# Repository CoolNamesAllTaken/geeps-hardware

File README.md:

# geeps-hardware
Pronounced Gee-Pee-Ess (hardware).

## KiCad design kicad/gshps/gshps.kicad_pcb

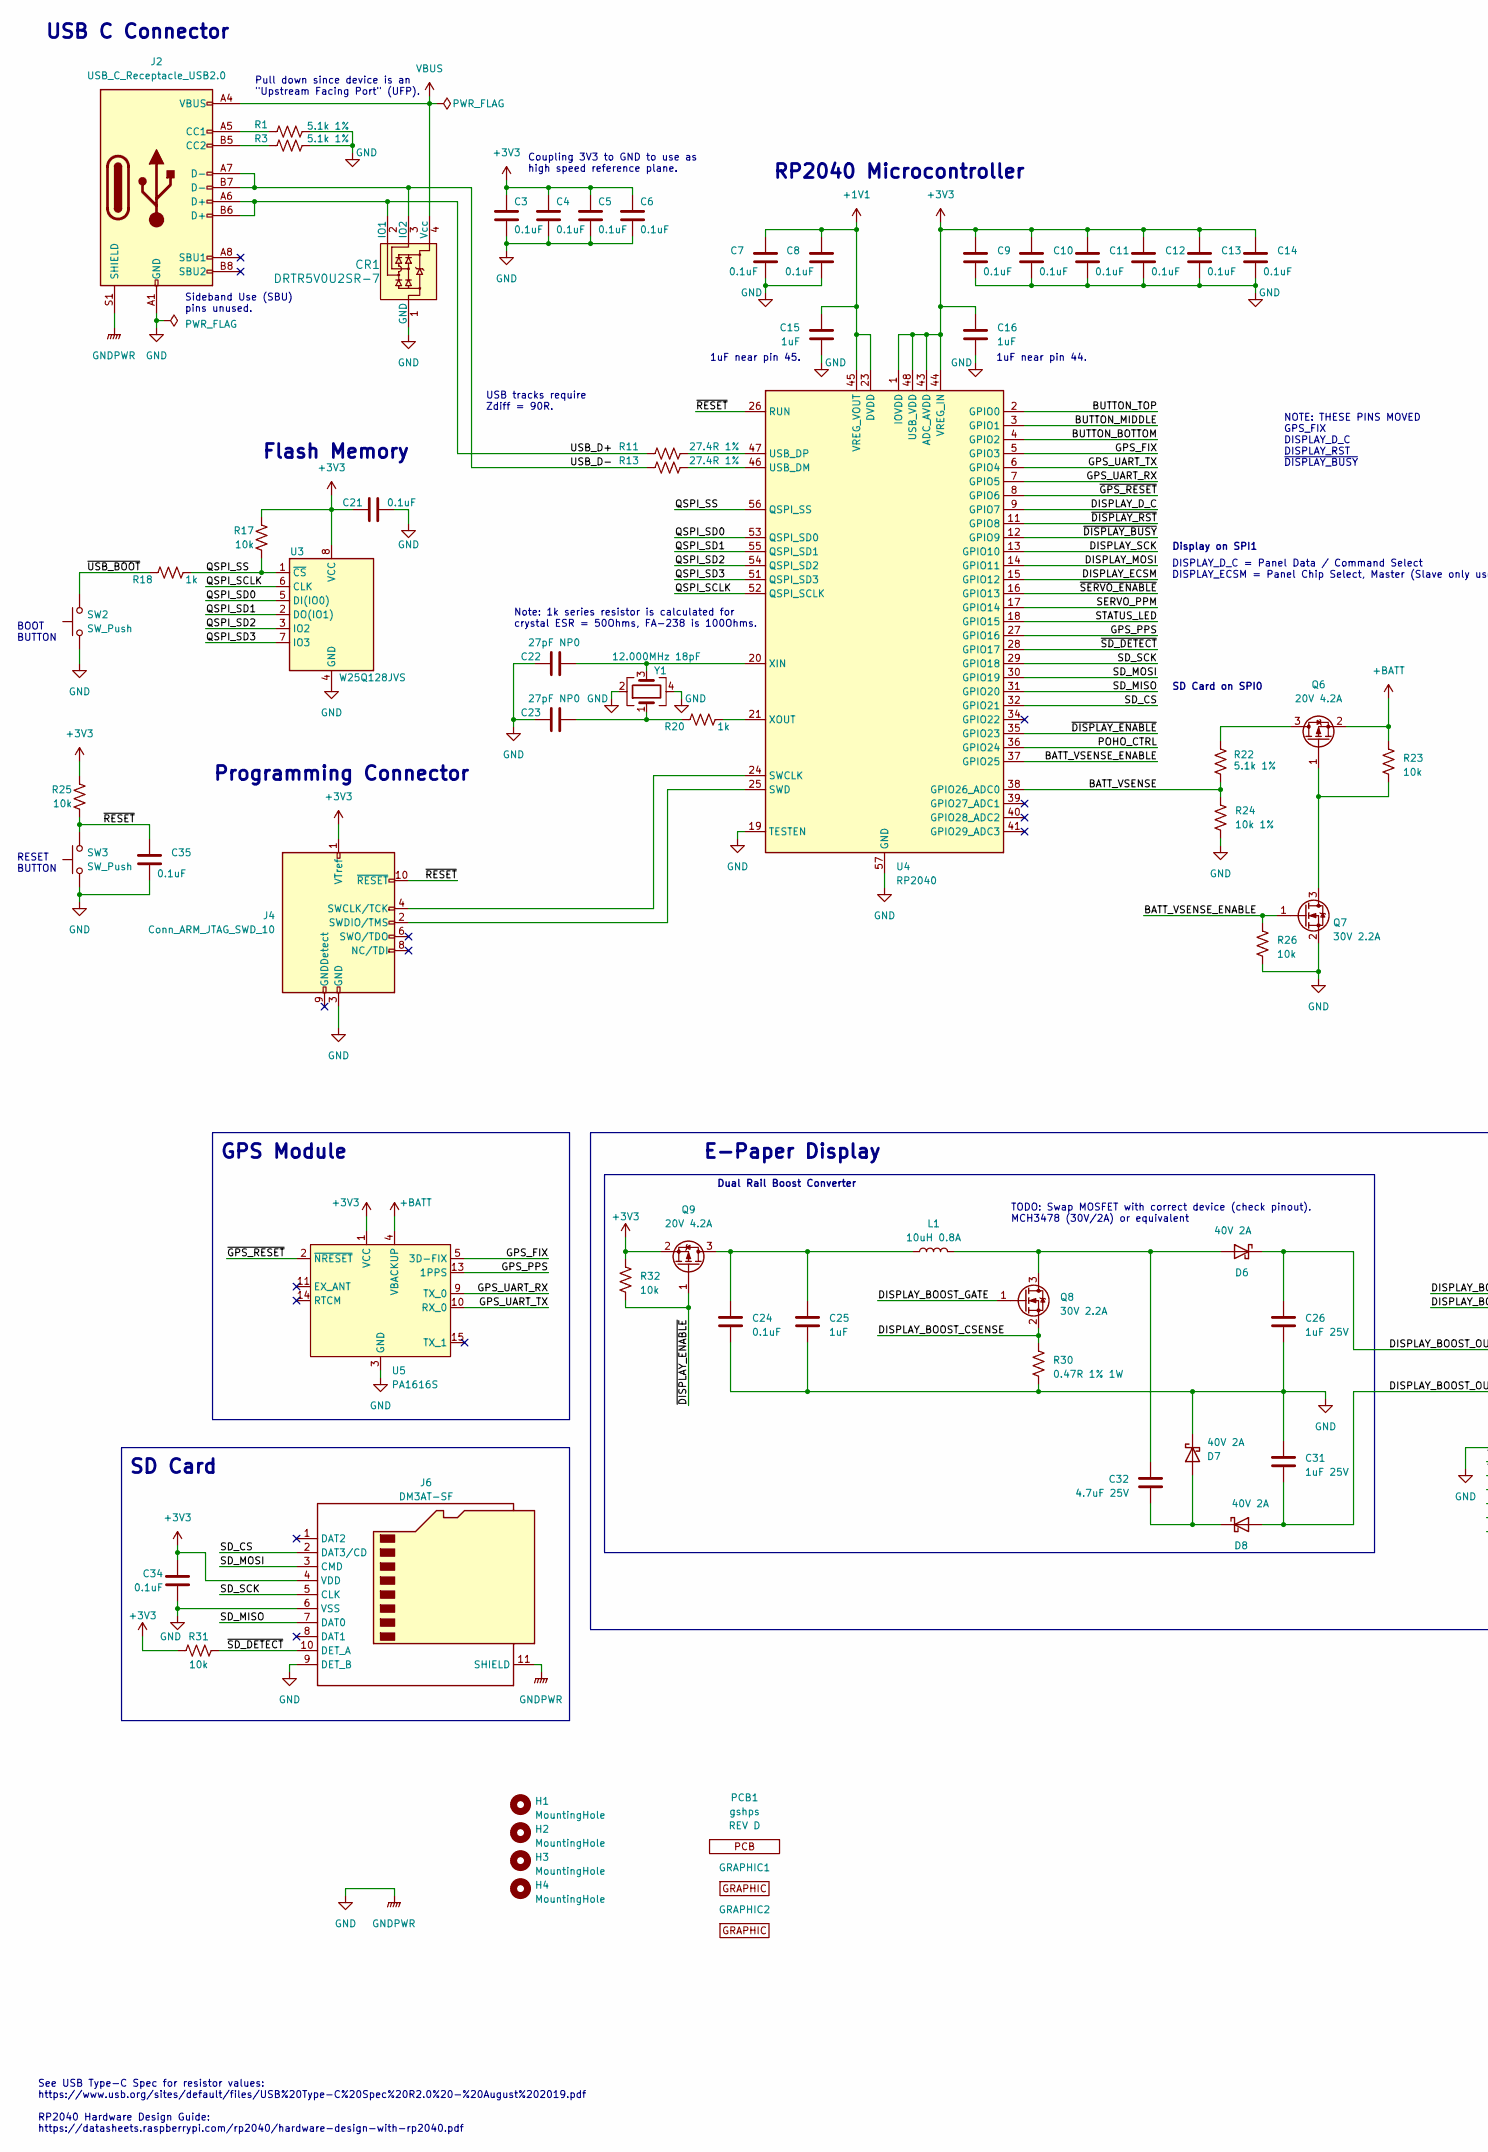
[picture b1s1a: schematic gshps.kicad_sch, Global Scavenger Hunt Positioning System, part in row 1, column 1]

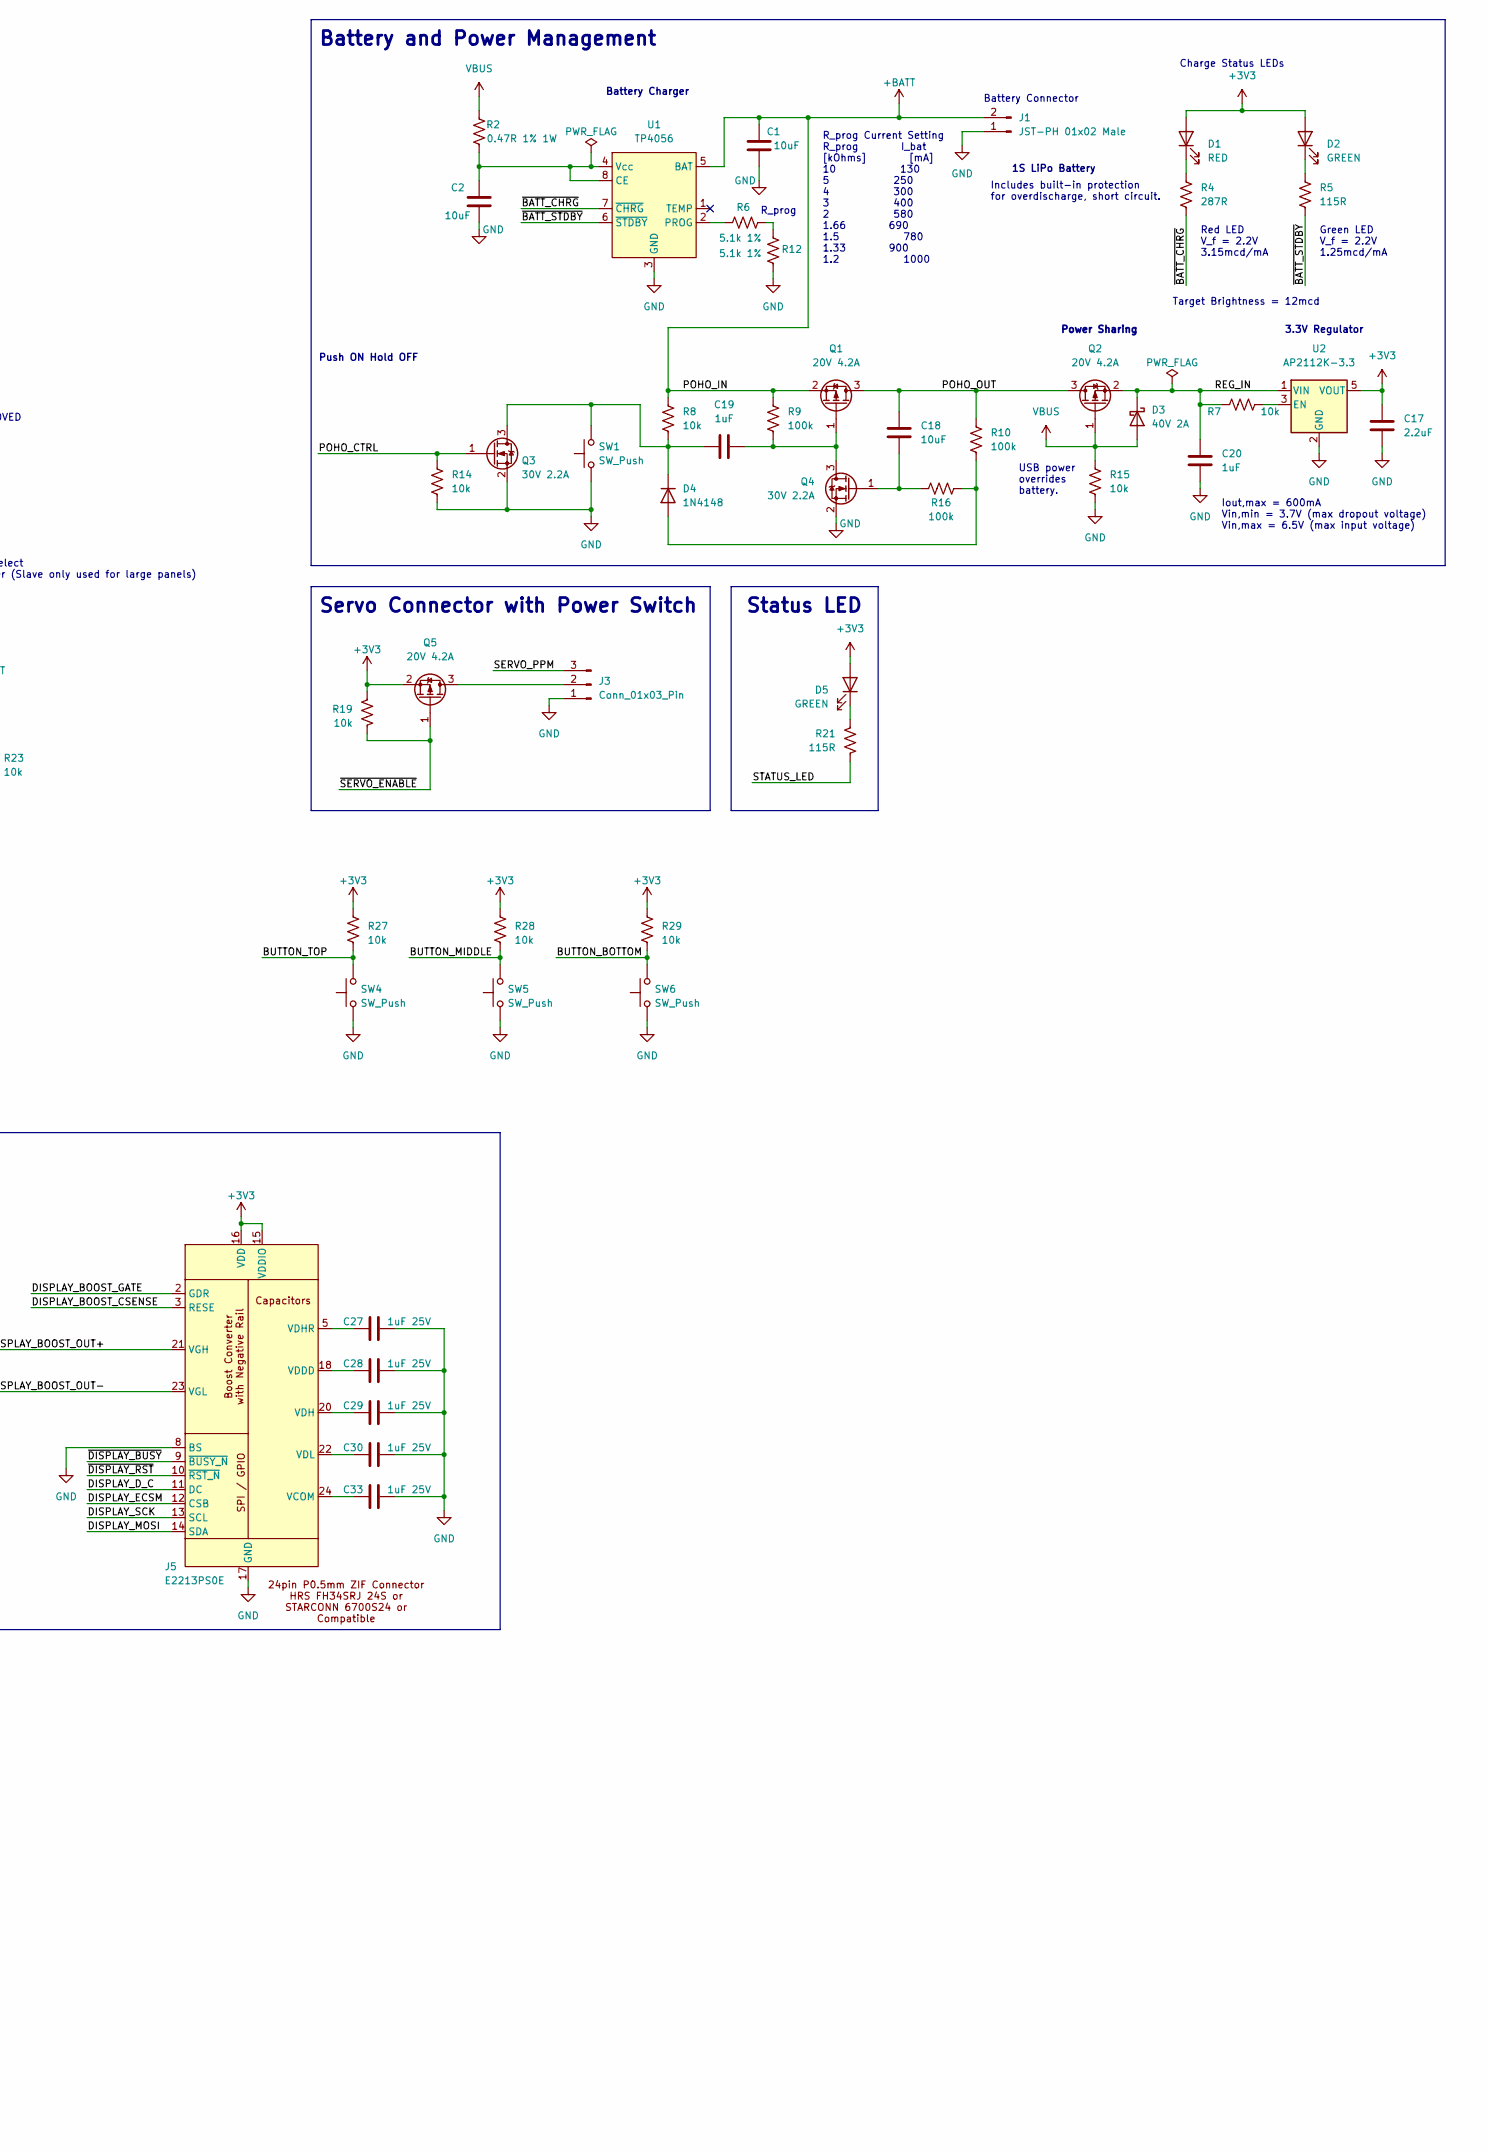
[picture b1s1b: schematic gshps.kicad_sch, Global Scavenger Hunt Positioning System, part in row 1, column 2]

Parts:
C1, C2, C18: 10uF; C_0805_2012Metric
C3, C4, C5, C6, C7, C8, C9, C10, C11, C12, C13, C14, C21, C24, C34, C35: 0.1uF; C_0402_1005Metric
C15, C16, C19, C20, C25: 1uF; C_0603_1608Metric
C17: 2.2uF; C_0603_1608Metric
C22, C23: 27pF NP0; C_0402_1005Metric
C26, C27, C28, C29, C30, C31, C33: 1uF 25V; C_0603_1608Metric
C32: 4.7uF 25V; C_0805_2012Metric
CR1: DRTR5V0U2SR-7; SOT-143; MPN DRTR5V0U2SR-7
D1: RED; LED_0603_1608Metric; MPN SML-D12U8WT86
D2, D5: GREEN; LED_0603_1608Metric; MPN SML-D12M8WT86
D3, D6, D7, D8: 40V 2A; D_SOD-123F; MPN SS2040FL_R1_00001
D4: 1N4148; D_SOD-123
GRAPHIC1: Graphic; BirdWithPants_Small_Right
GRAPHIC2: Graphic; BirdWithPants_Small_Left
H1, H2, H3, H4: MountingHole; MountingHole_2.7mm_M2.5_Isolated
J1: JST-PH 01x02 Male; JST_PH_S2B-PH-K_1x02_P2.00mm_Horizontal; MPN S2B-PH-K-S(LF)(SN)
J2: USB_C_Receptacle_USB2.0; USB_C_Receptacle_GCT_USB4115-03-C; MPN USB4115-03-C
J3: Conn_01x03_Pin; Molex_PicoBlade_53261-0371_1x03-1MP_P1.25mm_Horizontal; MPN 0532610371
J4: Conn_ARM_JTAG_SWD_10; PinHeader_2x05_P1.27mm_Vertical_SMD; MPN 4048
J5: E2213PS0E; Hirose_FH34SRJ-24S-0.5SH_1x24-1MP_P0.50mm_Horizontal_Mirror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; MPN FH34SRJ-24S-0.5SH(50)
J6: DM3AT-SF; microSD_HC_Hirose_DM3D-SF; MPN DM3AT-SF-PEJM5
L1: 10uH 0.8A; L_1008_2520Metric; MPN 74479887310A
PCB1: PCB; PCB_PN_REV; MPN gshps
Q1, Q2, Q5, Q6, Q9: 20V 4.2A; SOT-23; MPN DMG2305UX-7
Q3, Q4, Q7, Q8: 30V 2.2A; SOT-23; MPN DMN3200U-7
R1, R3, R6, R12, R22: 5.1k 1%; R_0402_1005Metric
R2, R30: 0.47R 1% 1W; R_2512_6332Metric; MPN RL2512FK-070R47L
R4: 287R; R_0402_1005Metric; MPN RC0402FR-07287RL
R5, R21: 115R; R_0402_1005Metric; MPN RC0402FR-07115RL
R7, R8, R14, R15, R17, R19, R23, R25, R26, R27, R28, R29, R31, R32: 10k; R_0402_1005Metric
R9, R10, R16: 100k; R_0402_1005Metric
R11, R13: 27.4R 1%; R_0402_1005Metric
R18, R20: 1k; R_0402_1005Metric
R24: 10k 1%; R_0402_1005Metric
SW1, SW2, SW3, SW4, SW5, SW6: SW_Push; SW_SPST_TL3342; MPN TL3342F160QG/TR
U1: TP4056; HSOP-8-1EP_3.9x4.9mm_P1.27mm_EP2.41x3.1mm_ThermalVias
U2: AP2112K-3.3; SOT-23-5; MPN AP2112K-3.3TRG1
U3: W25Q128JVS; SOIC-8_5.23x5.23mm_P1.27mm
U4: RP2040; QFN-56-1EP_7x7mm_P0.4mm_EP3.2x3.2mm
U5: PA1616S; MPN PA1616S
Y1: 12.000MHz 18pF; Crystal_SMD_SeikoEpson_FA238-4Pin_3.2x2.5mm; MPN FA-238V 12.0000MA-C5

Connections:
+1V1: C7.2, C8.2, C15.2, U4.23 (DVDD), U4.45 (VREG_VOUT), U4.50 (DVDD)
+3V3: C3.2, C4.2, C5.2, C6.2, C9.2, C10.2, C11.2, C12.2, C13.2, C14.2, C16.2, C17.1, C21.1, C34.1, D1.2 (A), D2.2 (A), D5.2 (A), J4.1 (VTref), J5.15 (VDDIO), J5.16 (VDD), J6.4 (VDD), Q5.2 (S), Q9.2 (S), R17.1, R19.1, R25.1, R27.1, R28.1, R29.1, R31.1, R32.1, U2.5 (VOUT), U3.8 (VCC), U4.1 (IOVDD), U4.10 (IOVDD), U4.22 (IOVDD), U4.33 (IOVDD), U4.42 (IOVDD), U4.43 (ADC_AVDD), U4.44 (VREG_IN), U4.48 (USB_VDD), U4.49 (IOVDD), U5.1 (VCC)
+BATT: C1.1, J1.2, Q1.2 (S), Q6.2 (S), R8.1, R9.1, R23.1, U1.5 (BAT), U5.4 (VBACKUP)
/BATT_VSENSE: R22.1, R24.1, U4.38 (GPIO26_ADC0)
/BATT_VSENSE_ENABLE: Q7.1 (G), R26.1, U4.37 (GPIO25)
/BUTTON_BOTTOM: R29.2, SW6.2, U4.4 (GPIO2)
/BUTTON_MIDDLE: R28.2, SW5.2, U4.3 (GPIO1)
/BUTTON_TOP: R27.2, SW4.2, U4.2 (GPIO0)
/DISPLAY_BOOST_CSENSE: J5.3 (RESE), Q8.2 (S), R30.1
/DISPLAY_BOOST_GATE: J5.2 (GDR), Q8.1 (G)
/DISPLAY_BOOST_OUT+: C26.1, D6.1 (K), J5.21 (VGH)
/DISPLAY_BOOST_OUT-: C31.2, D8.2 (A), J5.23 (VGL)
/DISPLAY_D_C: J5.11 (DC), U4.9 (GPIO7)
/DISPLAY_ECSM: J5.12 (CSB), U4.15 (GPIO12)
/DISPLAY_MOSI: J5.14 (SDA), U4.14 (GPIO11)
/DISPLAY_SCK: J5.13 (SCL), U4.13 (GPIO10)
/GPS_FIX: U4.5 (GPIO3), U5.5 (3D-FIX)
/GPS_PPS: U4.27 (GPIO16), U5.13 (1PPS)
/GPS_UART_RX: U4.7 (GPIO5), U5.9 (TX_0)
/GPS_UART_TX: U4.6 (GPIO4), U5.10 (RX_0)
/POHO_CTRL: Q3.1 (G), R14.1, U4.36 (GPIO24)
/POHO_OUT: C18.1, Q1.3 (D), Q2.3 (D), R10.1
/QSPI_SCLK: U3.6 (CLK), U4.52 (QSPI_SCLK)
/QSPI_SD0: U3.5 (DI(IO0)), U4.53 (QSPI_SD0)
/QSPI_SD1: U3.2 (DO(IO1)), U4.55 (QSPI_SD1)
/QSPI_SD2: U3.3 (IO2), U4.54 (QSPI_SD2)
/QSPI_SD3: U3.7 (IO3), U4.51 (QSPI_SD3)
/QSPI_SS: R17.2, R18.2, U3.1 (~CS), U4.56 (QSPI_SS)
/REG_IN: C20.1, D3.1 (K), Q2.2 (S), R7.1, U2.1 (VIN)
/SD_CS: J6.2 (DAT3/CD), U4.32 (GPIO21)
/SD_MISO: J6.7 (DAT0), U4.31 (GPIO20)
/SD_MOSI: J6.3 (CMD), U4.30 (GPIO19)
/SD_SCK: J6.5 (CLK), U4.29 (GPIO18)
/SERVO_PPM: J3.3, U4.17 (GPIO14)
/STATUS_LED: R21.2, U4.18 (GPIO15)
/USB_D+: CR1.2 (IO1), J2.A6 (D+), J2.B6 (D+), R11.1
/USB_D-: CR1.3 (IO2), J2.A7 (D-), J2.B7 (D-), R13.1
/~BATT_CHRG: R4.2, U1.7 (~CHRG)
/~BATT_STDBY: R5.2, U1.6 (~STDBY)
/~DISPLAY_BUSY: J5.9 (~BUSY_N), U4.12 (GPIO9)
/~DISPLAY_ENABLE: Q9.1 (G), R32.2, U4.35 (GPIO23)
/~DISPLAY_RST: J5.10 (~RST_N), U4.11 (GPIO8)
/~GPS_RESET: U4.8 (GPIO6), U5.2 (~NRESET)
/~RESET: C35.2, J4.10 (~RESET), R25.2, SW3.2, U4.26 (RUN)
/~SD_DETECT: J6.10 (DET_A), R31.2, U4.28 (GPIO17)
/~SERVO_ENABLE: Q5.1 (G), R19.2, U4.16 (GPIO13)
/~USB_BOOT: R18.1, SW2.2
GND: C1.2, C2.2, C3.1, C4.1, C5.1, C6.1, C7.1, C8.1, C9.1, C10.1, C11.1, C12.1, C13.1, C14.1, C15.1, C16.1, C17.2, C20.2, C21.2, C22.1, C23.1, C24.2, C25.2, C26.2, C27.2, C28.2, C29.2, C30.2, C31.1, C33.2, C34.2, C35.1, CR1.1 (GND), D7.1 (K), J1.1, J2.A1 (GND), J2.A12 (GND), J2.B1 (GND), J2.B12 (GND), J2.S1 (SHIELD), J3.1, J4.3 (GND), J4.5 (GND), J5.8 (BS), J5.17 (GND), J6.6 (VSS), J6.9 (DET_B), J6.11 (SHIELD), Q3.2 (S), Q4.2 (S), Q7.2 (S), R1.2, R3.2, R12.1, R14.2, R15.2, R24.2, R26.2, R30.2, SW1.1, SW2.1, SW3.1, SW4.1, SW5.1, SW6.1, U1.3 (GND), U1.9 (GND), U2.2 (GND), U3.4 (GND), U4.19 (TESTEN), U4.57 (GND), U5.3 (GND), U5.8 (GND), U5.12 (GND), U5.19 (GND), Y1.2, Y1.4
unnamed: C23.2, R20.1, Y1.1
unnamed: D1.1 (K), R4.1
unnamed: D2.1 (K), R5.1
unnamed: D4.2 (A), R10.2, R16.2
unnamed: C19.1, D4.1 (K), Q3.3 (D), R8.2, SW1.2
unnamed: D5.1 (K), R21.1
unnamed: C32.1, D6.2 (A), L1.2, Q8.3 (D)
unnamed: C32.2, D7.2 (A), D8.1 (K)
unnamed: J2.A5 (CC1), R1.1
unnamed: J2.B5 (CC2), R3.1
unnamed: J3.2, Q5.3 (D)
unnamed: J4.4 (SWCLK/TCK), U4.24 (SWCLK)
unnamed: J4.2 (SWDIO/TMS), U4.25 (SWD)
unnamed: C33.1, J5.24 (VCOM)
unnamed: C28.1, J5.18 (VDDD)
unnamed: C29.1, J5.20 (VDH)
unnamed: C27.1, J5.5 (VDHR)
unnamed: C30.1, J5.22 (VDL)
unnamed: C19.2, Q1.1 (G), Q4.3 (D), R9.2
unnamed: C18.2, Q4.1 (G), R16.1
unnamed: Q6.3 (D), R22.2
unnamed: Q6.1 (G), Q7.3 (D), R23.2
unnamed: C24.1, C25.1, L1.1, Q9.3 (D)
unnamed: R6.2, R12.2
unnamed: C2.1, R2.2, U1.4 (Vcc), U1.8 (CE)
unnamed: R6.1, U1.2 (PROG)
unnamed: R7.2, U2.3 (EN)
unnamed: R13.2, U4.46 (USB_DM)
unnamed: R11.2, U4.47 (USB_DP)
unnamed: C22.2, U4.20 (XIN), Y1.3
unnamed: R20.2, U4.21 (XOUT)
VBUS: CR1.4 (Vcc), D3.2 (A), J2.A4 (VBUS), J2.A9 (VBUS), J2.B4 (VBUS), J2.B9 (VBUS), Q2.1 (G), R2.1, R15.1

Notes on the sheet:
NOTE: THESE PINS MOVED GPS_FIX DISPLAY_D_C DISPLAY_RST ~{DISPLAY_BUSY}
Flash Memory
1uF near pin 45.
Red LED V_f = 2.2V 3.15mcd/mA
Battery Connector
TODO: Swap MOSFET with correct device (check pinout). MCH3478 (30V/2A) or equivalent
DISPLAY_D_C = Panel Data / Command Select DISPLAY_ECSM = Panel Chip Select, Master (Slave only used for large panels)
SD Card
USB power overrides battery.
3.3V Regulator
USB tracks require Zdiff = 90R.
Battery Charger
Power Sharing
Iout,max = 600mA Vin,min = 3.7V (max dropout voltage) Vin,max = 6.5V (max input voltage)
Battery and Power Management
Push ON Hold OFF
Servo Connector with Power Switch
Green LED V_f = 2.2V 1.25mcd/mA
GPS Module
Display on SPI1
Status LED
Dual Rail Boost Converter
Coupling 3V3 to GND to use as high speed reference plane.
SD Card on SPI0
RESET BUTTON
Charge Status LEDs
Programming Connector
BOOT BUTTON
1uF near pin 44.
E-Paper Display
RP2040 Microcontroller
Note: 1k series resistor is calculated for crystal ESR = 50Ohms, FA-238 is 100Ohms.
Target Brightness = 12mcd
R_prog Current Setting R_prog I_bat [kOhms] [mA] 10 130 5 250 4 300 3 400 2 580 1.66 690 1.5 780 1.33 900 1.2 1000
R_prog
Sideband Use (SBU) pins unused.
Includes built-in protection for overdischarge, short circuit.
See USB Type-C Spec for resistor values: https://www.usb.org/sites/default/files/USB%20Type-C%20Spec%20R2.0%20-%20August%202019.pdf RP2040 Hardware Design Guide: https://datasheets.raspberrypi.com/rp2040/hardware-design-with-rp2040.pdf
1S LiPo Battery
USB C Connector

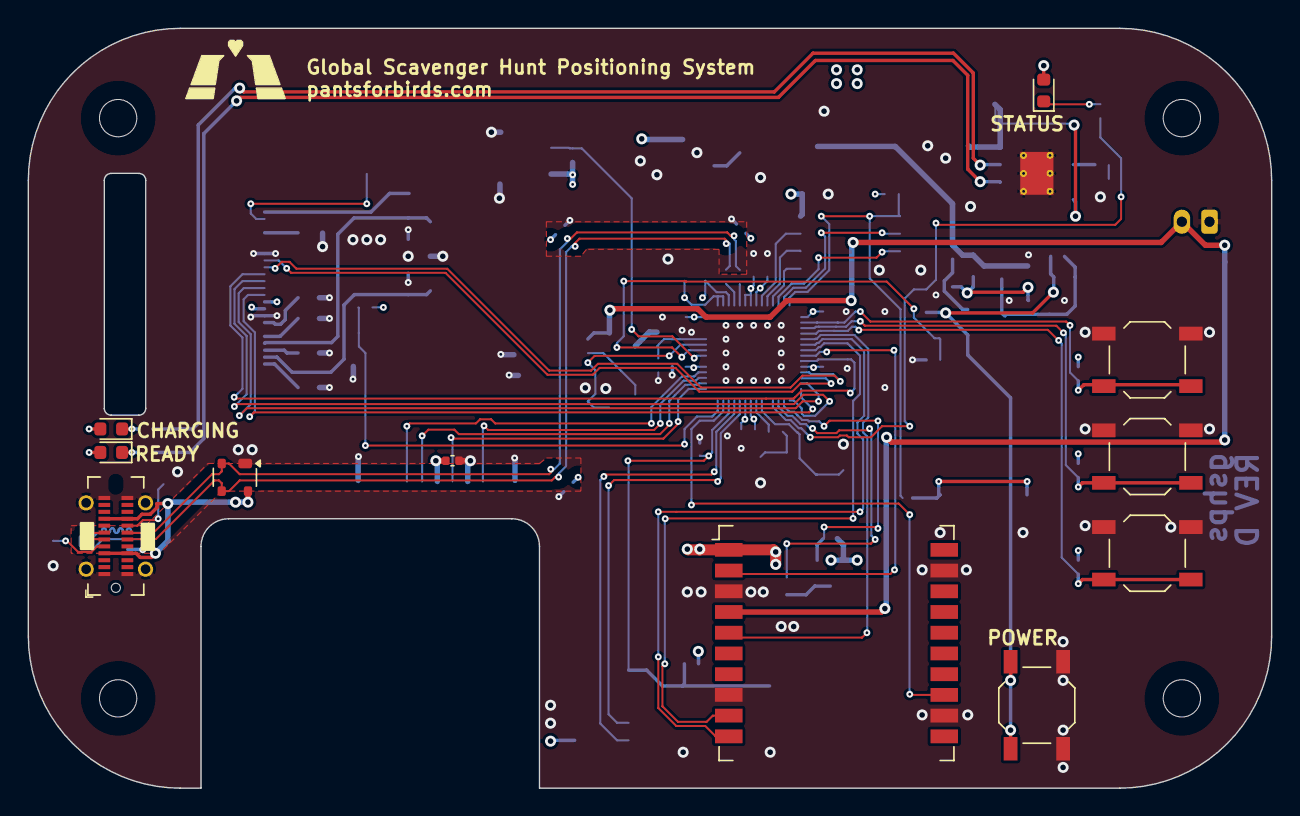
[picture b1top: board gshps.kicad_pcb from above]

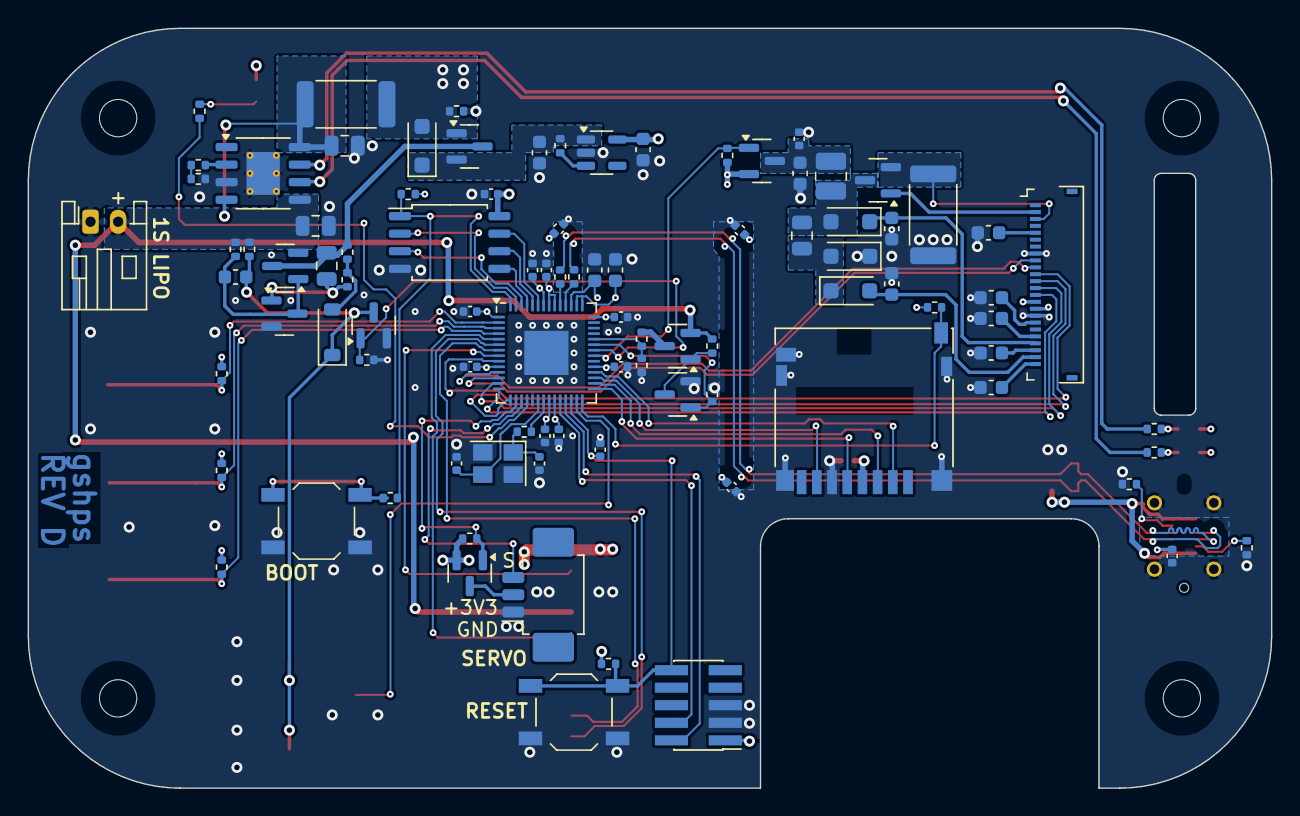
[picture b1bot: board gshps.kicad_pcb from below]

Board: 4 copper layers, 90.0 x 55.0 mm, 111 parts (94 on the bottom side), 80 nets.

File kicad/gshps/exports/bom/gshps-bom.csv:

"Reference","Value","Datasheet","Footprint","Qty","DNP","MPN","Standard Cost"
"C1,C2,C18","10uF","~","Capacitor_SMD:C_0805_2012Metric","3","","",""
"C3,C4,C5,C6,C7,C8,C9,C10,C11,C12,C13,C14,C21,C24,C34,C35","0.1uF","~","Capacitor_SMD:C_0402_1005Metric","16","","",""
"C15,C16,C19,C20,C25","1uF","~","Capacitor_SMD:C_0603_1608Metric","5","","",""
"C17","2.2uF","~","Capacitor_SMD:C_0603_1608Metric","1","","",""
"C22,C23","27pF NP0","~","Capacitor_SMD:C_0402_1005Metric","2","","",""
"C26,C27,C28,C29,C30,C31,C33","1uF 25V","~","Capacitor_SMD:C_0603_1608Metric","7","","",""
"C32","4.7uF 25V","~","Capacitor_SMD:C_0805_2012Metric","1","","",""
"CR1","DRTR5V0U2SR-7","","Package_TO_SOT_SMD:SOT-143","1","","DRTR5V0U2SR-7","0.11"
"D1","RED","~","LED_SMD:LED_0603_1608Metric","1","","SML-D12U8WT86","0.07"
"D2,D5","GREEN","https://fscdn.rohm.com/en/products/databook/datasheet/opto/l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","LED_SMD:LED_0603_1608Metric","2","","SML-D12M8WT86","0.07"
"D3,D6,D7,D8","40V 2A","~","Diode_SMD:D_SOD-123F","4","","SS2040FL_R1_00001","0.10"
"D4","1N4148","~","Diode_SMD:D_SOD-123","1","","",""
"H1,H2,H3,H4","MountingHole","~","Custom_MountingHole:MountingHole_2.7mm_M2.5_Isolated","4","","",""
"J1","JST-PH 01x02 Male","~","Connector_JST:JST_PH_S2B-PH-K_1x02_P2.00mm_Horizontal","1","","S2B-PH-K-S(LF)(SN)","0.02"
"J2","USB_C_Receptacle_USB2.0","https://www.usb.org/sites/default/files/documents/usb_type-c.zip","Custom_Connector_USB:USB_C_Receptacle_GCT_USB4115-03-C","1","","USB4115-03-C","0.67"
"J3","Conn_01x03_Pin","~","Connector_Molex:Molex_PicoBlade_53261-0371_1x03-1MP_P1.25mm_Horizontal","1","","0532610371","0.37"
"J4","Conn_ARM_JTAG_SWD_10","http://infocenter.arm.com/help/topic/com.arm.doc.ddi0314h/DD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","Connector_PinHeader_1.27mm:PinHeader_2x05_P1.27mm_Vertical_SMD","1","","4048","1.95"
"J5","E2213PS0E","https://www.mouser.com/datasheet/2/185/FH34SRJ_24S_0_5SH_99_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","Custom_FFC-FPC:Hirose_FH34SRJ-24S-0.5SH_1x24-1MP_P0.50mm_Horizontal_Mirrored","1","","FH34SRJ-24S-0.5SH(50)","0.61"
"J6","DM3AT-SF","https://www.hirose.com/product/en/download_file/key_name/DM3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","Connector_Card:microSD_HC_Hirose_DM3D-SF","1","","DM3AT-SF-PEJM5","1.88"
"L1","10uH 0.8A","~","Inductor_SMD:L_1008_2520Metric","1","","74479887310A","0.93"
"Q1,Q2,Q5,Q6,Q9","20V 4.2A","~","Package_TO_SOT_SMD:SOT-23","5","","DMG2305UX-7","0.08"
"Q3,Q4,Q7,Q8","30V 2.2A","-- mixed values --","Package_TO_SOT_SMD:SOT-23","4","","DMN3200U-7","0.14"
"R1,R3,R6,R12,R22","5.1k 1%","~","Resistor_SMD:R_0402_1005Metric","5","","",""
"R2,R30","0.47R 1% 1W","~","Resistor_SMD:R_2512_6332Metric","2","","RL2512FK-070R47L","0.14"
"R4","287R","~","Resistor_SMD:R_0402_1005Metric","1","","RC0402FR-07287RL","0.01"
"R5,R21","115R","~","Resistor_SMD:R_0402_1005Metric","2","","RC0402FR-07115RL","0.01"
"R7,R8,R14,R15,R17,R19,R23,R25,R26,R27,R28,R29,R31,R32","10k","~","Resistor_SMD:R_0402_1005Metric","14","","",""
"R9,R10,R16","100k","~","Resistor_SMD:R_0402_1005Metric","3","","",""
"R11,R13","27.4R 1%","~","Resistor_SMD:R_0402_1005Metric","2","","",""
"R18,R20","1k","~","Resistor_SMD:R_0402_1005Metric","2","","",""
"R24","10k 1%","~","Resistor_SMD:R_0402_1005Metric","1","","",""
"SW1,SW2,SW3,SW4,SW5,SW6","SW_Push","~","Button_Switch_SMD:SW_SPST_TL3342","6","","TL3342F160QG/TR","0.40"
"U1","TP4056","https://dlnmh9ip6v2uc.cloudfront.net/datasheets/Prototyping/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","Package_SO:HSOP-8-1EP_3.9x4.9mm_P1.27mm_EP2.41x3.1mm_ThermalVias","1","","",""
"U2","AP2112K-3.3","https://www.diodes.com/assets/Datasheets/AP2112.pdf","Package_TO_SOT_SMD:SOT-23-5","1","","AP2112K-3.3TRG1","0.12"
"U3","W25Q128JVS","http://www.winbond.com/resource-files/w25q128jv_dtr%20revc%2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","Custom_Package_SO:SOIC-8_5.23x5.23mm_P1.27mm","1","","",""
"U4","RP2040","https://datasheets.raspberrypi.com/rp2040/rp2040-datasheet.pdf","Package_DFN_QFN:QFN-56-1EP_7x7mm_P0.4mm_EP3.2x3.2mm","1","","",""
"U5","PA1616S","","Custom_Module:PA1616S","1","","PA1616S","10.00"
"Y1","12.000MHz 18pF","~","Crystal:Crystal_SMD_SeikoEpson_FA238-4Pin_3.2x2.5mm","1","","FA-238V 12.0000MA-C5","0.61"

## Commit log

2022-09-24 Add proto
2023-06-24 Make geeps mk1 schematic first pass
2023-09-03 Routing for geeps mk1
2023-09-10 GSHPS Rev A
2025-01-07 Make gshps rev B
2025-02-16 Make gshps rev C
2025-02-24 Fix BOM export
2025-02-26 Design enclosure
2025-02-28 GSHPS enclosure
2025-02-28 Change button height and make access hatch self centering
2025-03-05 Save progress before changing access hatch
2025-03-06 Save progress before changing access hatch latch shape.
2025-03-13 Clean up after proposal
